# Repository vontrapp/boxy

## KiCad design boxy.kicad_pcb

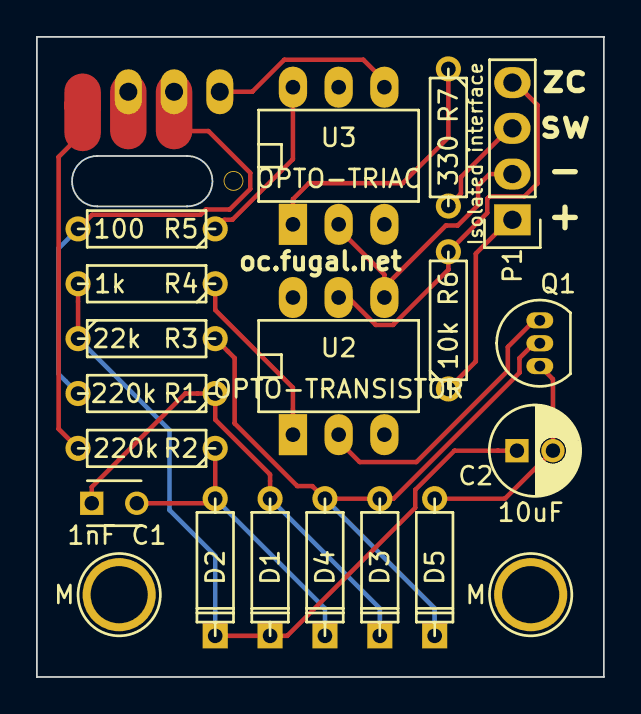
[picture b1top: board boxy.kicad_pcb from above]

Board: 2 copper layers, 31.5 x 35.6 mm, 21 parts (1 on the bottom side), 15 nets.

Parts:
C1: 1nF; C_Disc_D3_P2.5
C2: 10uF; C_Radial_D5_L11_P2
D1, D2, D3, D4, D5: D; D3
M: 1pin
M#2: 1pin
P1: Isolated interface; Socket_Strip_Straight_1x04
Q1: NPN; TO-92_Inline_Narrow_Oval
R1, R2: 220k; R3
R3: 22k; R3
R4: 1k; R3
R5: 100; R3
R6: 10k; R3
R7: 330; R3
U1: TRIAC; TO-220_Neutral123_Vertical
U2: OPTO-TRANSISTOR; DIP-6__300_ELL
U3: OPTO-TRIAC; DIP-6__300_ELL

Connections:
Hot: R1.2, R5.2, U1.2
unnamed: C1.1, D1.1, D3.2, R1.1
unnamed: C1.2, D2.1, D4.2, R2.1
unnamed: C2.1, D1.2, D2.2, R3.1, R4.2
unnamed: C2.2, D5.1, Q1.1
unnamed: D3.1, D4.1, D5.2, Q1.2, R3.2
unnamed: P1.1, R6.1
unnamed: P1.2, U2.4, U3.2
unnamed: P1.3, R7.2
unnamed: P1.4, R6.2, U2.5
unnamed: Q1.3, U2.2
unnamed: R4.1, U2.1
unnamed: R5.1, U3.6
unnamed: R7.1, U3.1
unnamed: U1.3, U3.4

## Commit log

2015-10-10 boxy through hole
2015-10-10 revamp through hole version, add logos
2015-10-10 add edge cuts, remove logo REF
2015-10-10 Change c2 footprint to one with 3d
2015-10-11 boxy with smd resistors
2015-10-12 use edge-cut for wire slot
2015-10-12 latest OC logo
